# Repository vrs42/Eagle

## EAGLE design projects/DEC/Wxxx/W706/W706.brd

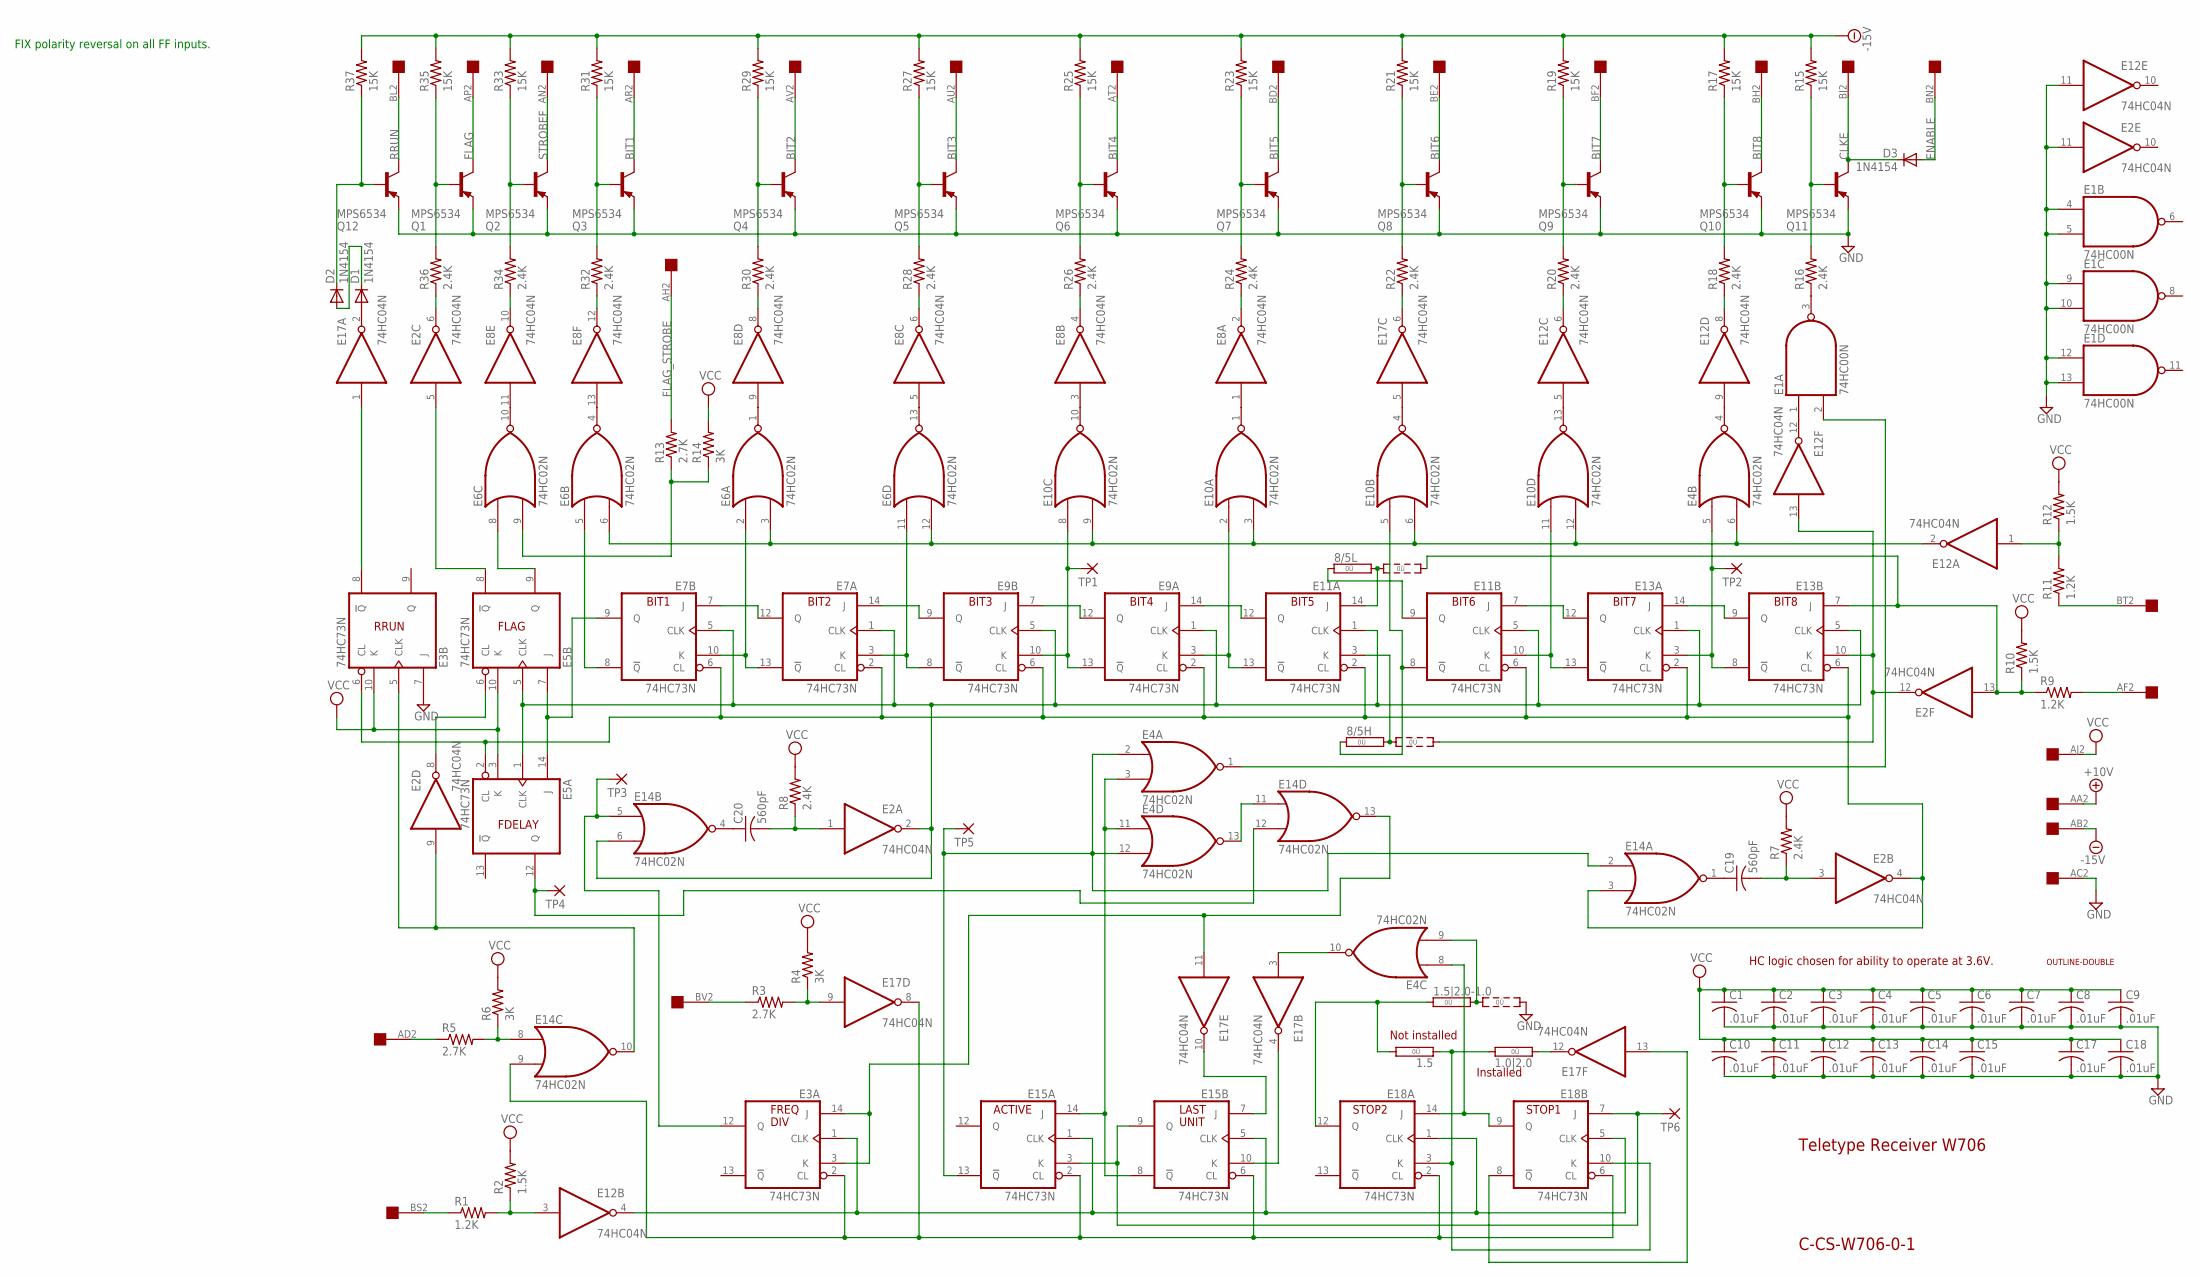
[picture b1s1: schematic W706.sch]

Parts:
1.0|2.0, 1.5: 0R; 0R/10
1.5|2.0-1.0, 8/5H, 8/5L: 0R2; 0R2/10
C1, C2, C3, C4, C5, C6, C7, C8, C9, C10, C11, C12, C13, C14, C15, C17, C18: .01uF; C050-025X075
C19, C20: 560pF; C050-025X075
D1, D2, D3: 1N4154; DO35-10
E1: 74HC00N; DIL14
E2, E8, E12, E17: 74HC04N; DIL14
E3, E5, E7, E9, E11, E13, E15, E18: 74HC73N; DIL14
E4, E6, E10, E14: 74HC02N; DIL14
Q1, Q2, Q3, Q4, Q5, Q6, Q7, Q8, Q9, Q10, Q11, Q12: MPS6534; TO39
R1, R9, R11: 1.2K; 0207/10
R2, R10, R12: 1.5K; 0207/10
R3, R5, R13: 2.7K; 0207/10
R4, R6, R14: 3K; 0207/10
R7, R8, R16, R18, R20, R22, R24, R26, R28, R30, R32, R34, R36: 2.4K; 0207/10
R15, R17, R19, R21, R23, R25, R27, R29, R31, R33, R35, R37: 15K; 0207/10
TP1, TP2, TP3, TP4, TP5, TP6: 3,17/1,3
U$1: OUTLINE-DOUBLE; DOUBLE
U$2: DOUBLE; EDGE-CON4

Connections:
+10V: U$2.AA2
-15V: R15.2, R17.2, R19.2, R21.2, R23.2, R25.2, R27.2, R29.2, R31.2, R33.2, R35.2, R37.2, U$2.AB2
BIT1: Q3.3 (C), U$2.AR2
BIT2: Q4.3 (C), U$2.AV2
BIT3: Q5.3 (C), U$2.AU2
BIT4: Q6.3 (C), U$2.AT2
BIT5: Q7.3 (C), U$2.BD2
BIT6: Q8.3 (C), U$2.BE2
BIT7: Q9.3 (C), U$2.BF2
BIT8: Q10.3 (C), U$2.BH2
CLKE: D3.C, Q11.3 (C), U$2.BJ2
ENABLE: D3.A, U$2.BN2
FLAG: Q1.3 (C), U$2.AP2
FLAG_STROBE: R13.2, U$2.AH2
GND: 1.5|2.0-1.0.3, C1.2, C2.2, C3.2, C4.2, C5.2, C6.2, C7.2, C8.2, C9.2, C10.2, C11.2, C12.2, C13.2, C14.2, C15.2, C17.2, C18.2, E1.4 (I0), E1.5 (I1), E1.7 (GND), E1.9 (I0), E1.10 (I1), E1.12 (I0), E1.13 (I1), E2.7 (GND), E2.11 (I), E3.7 (J), E3.11 (GND), E4.7 (GND), E5.11 (GND), E6.7 (GND), E7.11 (GND), E8.7 (GND), E9.11 (GND), E10.7 (GND), E11.11 (GND), E12.7 (GND), E12.11 (I), E13.11 (GND), E14.7 (GND), E15.11 (GND), E17.7 (GND), E18.11 (GND), Q1.1 (E), Q2.1 (E), Q3.1 (E), Q4.1 (E), Q5.1 (E), Q6.1 (E), Q7.1 (E), Q8.1 (E), Q9.1 (E), Q10.1 (E), Q11.1 (E), Q12.1 (E), U$2.AC2
unnamed: E6.1 (O), E8.9 (I)
unnamed: E6.4 (O), E8.13 (I)
unnamed: E6.10 (O), E8.11 (I)
unnamed: E6.13 (O), E8.5 (I)
unnamed: E8.1 (I), E10.1 (O)
unnamed: E10.4 (O), E17.5 (I)
unnamed: E10.13 (O), E12.5 (I)
unnamed: E8.3 (I), E10.10 (O)
unnamed: E4.4 (O), E12.9 (I)
unnamed: D1.A, E17.2 (O)
unnamed: D1.C, D2.A
unnamed: D2.C, Q12.2 (B), R37.1
unnamed: E1.3 (O), R16.1
unnamed: E12.8 (O), R18.1
unnamed: E12.6 (O), R20.1
unnamed: E17.6 (O), R22.1
unnamed: E8.2 (O), R24.1
unnamed: E8.4 (O), R26.1
unnamed: E8.6 (O), R28.1
unnamed: E8.8 (O), R30.1
unnamed: E8.12 (O), R32.1
unnamed: E2.6 (O), R36.1
unnamed: Q1.2 (B), R35.1, R36.2
unnamed: E8.10 (O), R34.1
unnamed: Q2.2 (B), R33.1, R34.2
unnamed: Q3.2 (B), R31.1, R32.2
unnamed: Q4.2 (B), R29.1, R30.2
unnamed: Q5.2 (B), R27.1, R28.2
unnamed: Q6.2 (B), R25.1, R26.2
unnamed: Q7.2 (B), R23.1, R24.2
unnamed: Q8.2 (B), R21.1, R22.2
unnamed: Q9.2 (B), R19.1, R20.2
unnamed: Q10.2 (B), R17.1, R18.2
unnamed: Q11.2 (B), R15.1, R16.2
unnamed: E3.8 (!Q), E17.1 (I)
unnamed: E2.5 (I), E5.8 (!Q)
unnamed: E5.9 (Q), E6.8 (I0)
unnamed: E7.7 (J), E7.12 (Q)
unnamed: E6.2 (I0), E7.10 (K), E7.13 (!Q)
unnamed: E2.2 (O), E5.1 (CLK), E5.5 (CLK), E7.1 (CLK), E7.5 (CLK), E9.1 (CLK), E9.5 (CLK), E11.1 (CLK), E11.5 (CLK), E13.1 (CLK), E13.5 (CLK), E14.6 (I1)
unnamed: E2.4 (O), E3.6 (CL), E5.2 (CL), E7.2 (CL), E7.6 (CL), E9.2 (CL), E9.6 (CL), E11.2 (CL), E11.6 (CL), E13.2 (CL), E13.6 (CL), E14.3 (I1)
unnamed: E6.11 (I0), E7.3 (K), E9.8 (!Q)
unnamed: E7.14 (J), E9.9 (Q)
unnamed: E9.10 (K), E9.13 (!Q), E10.8 (I0), TP1.1
unnamed: E9.7 (J), E9.12 (Q)
unnamed: E10.11 (I0), E11.10 (K), E13.13 (!Q)
unnamed: E11.7 (J), E13.12 (Q)
unnamed: E9.3 (K), E10.2 (I0), E11.13 (!Q)
unnamed: E9.14 (J), E11.12 (Q)
unnamed: 8/5H.1, E10.5 (I0), E11.8 (!Q)
unnamed: 8/5L.1, E11.9 (Q)
unnamed: E4.5 (I0), E13.3 (K), E13.8 (!Q), TP2.1
unnamed: E13.9 (Q), E13.14 (J)
unnamed: R1.1, U$2.BS2
unnamed: E4.6 (I1), E6.3 (I1), E6.6 (I1), E6.12 (I1), E10.3 (I1), E10.6 (I1), E10.9 (I1), E10.12 (I1), E12.2 (O)
unnamed: E6.5 (I0), E7.8 (!Q)
unnamed: E12.3 (I), R1.2, R2.1
unnamed: R11.1, U$2.BT2
unnamed: E12.1 (I), R11.2, R12.1
unnamed: E4.3 (I1), E4.11 (I0), E15.8 (!Q), E15.14 (J)
unnamed: E2.9 (I), E3.5 (CLK), E14.10 (O)
unnamed: E4.8 (I0), E18.9 (Q), E18.14 (J)
unnamed: E15.3 (K), E15.9 (Q), E18.7 (J), TP6.1
unnamed: E1.2 (I1), E4.1 (O)
unnamed: 8/5L.3, E2.13 (I), E13.7 (J), R9.1, R10.1
unnamed: 8/5H.2, E11.3 (K)
unnamed: 8/5L.2, E11.14 (J)
unnamed: E14.8 (I0), R5.2, R6.1
unnamed: R9.2, U$2.AF2
unnamed: 8/5H.3, E2.12 (O), E12.13 (I), E13.10 (K)
unnamed: E6.9 (I1), R13.1, R14.1
unnamed: R5.1, U$2.AD2
unnamed: E4.2 (I0), E4.12 (I1), E14.2 (I0), E15.13 (!Q), TP5.1
unnamed: E2.8 (O), E5.6 (CL)
unnamed: E3.1 (CLK), E12.4 (O), E15.1 (CLK), E15.5 (CLK), E18.1 (CLK), E18.5 (CLK)
unnamed: 1.5|2.0-1.0.2, E4.9 (I1)
unnamed: E17.9 (I), R3.2, R4.1
unnamed: R3.1, U$2.BV2
unnamed: E4.10 (O), E17.3 (I)
unnamed: E3.2 (CL), E14.9 (I1), E15.2 (CL), E15.6 (CL), E17.8 (O), E18.2 (CL), E18.6 (CL)
unnamed: 1.0|2.0.2, 1.5.1, E18.3 (K), E18.10 (K)
unnamed: 1.5.2, 1.5|2.0-1.0.1, E18.12 (Q)
unnamed: E15.10 (K), E17.4 (O)
unnamed: E4.13 (O), E14.11 (I0)
unnamed: C20.2, E2.1 (I), R8.1
unnamed: C19.2, E2.3 (I), R7.1
unnamed: C20.1, E14.4 (O)
unnamed: C19.1, E14.1 (O)
unnamed: 1.0|2.0.1, E17.12 (O)
unnamed: E17.13 (I), E18.8 (!Q)
unnamed: E3.12 (Q), E14.5 (I0), TP3.1
unnamed: E5.7 (J), E5.14 (J), E7.9 (Q)
unnamed: E15.7 (J), E17.10 (O)
unnamed: E5.12 (Q), E14.12 (I1), TP4.1
unnamed: E3.3 (K), E3.14 (J), E14.13 (O), E17.11 (I)
unnamed: E1.1 (I0), E12.12 (O)
RRUN: Q12.3 (C), U$2.BL2
STROBEF: Q2.3 (C), U$2.AN2
VCC: C1.1, C2.1, C3.1, C4.1, C5.1, C6.1, C7.1, C8.1, C9.1, C10.1, C11.1, C12.1, C13.1, C14.1, C15.1, C17.1, C18.1, E1.14 (VCC), E2.14 (VCC), E3.4 (VCC), E3.10 (K), E4.14 (VCC), E5.3 (K), E5.4 (VCC), E5.10 (K), E6.14 (VCC), E7.4 (VCC), E8.14 (VCC), E9.4 (VCC), E10.14 (VCC), E11.4 (VCC), E12.14 (VCC), E13.4 (VCC), E14.14 (VCC), E15.4 (VCC), E17.14 (VCC), E18.4 (VCC), R2.2, R4.2, R6.2, R7.2, R8.2, R10.2, R12.2, R14.2, U$2.AJ2

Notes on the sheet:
Teletype Receiver W706
C-CS-W706-0-1
BIT1
BIT2
BIT3
BIT4
BIT5
BIT6
BIT7
BIT8
RRUN
FLAG
FDELAY
STOP1
STOP2
LAST
UNIT
ACTIVE
FREQ
DIV
Not installed
Installed
HC logic chosen for ability to operate at 3.6V.
FIX polarity reversal on all FF inputs.

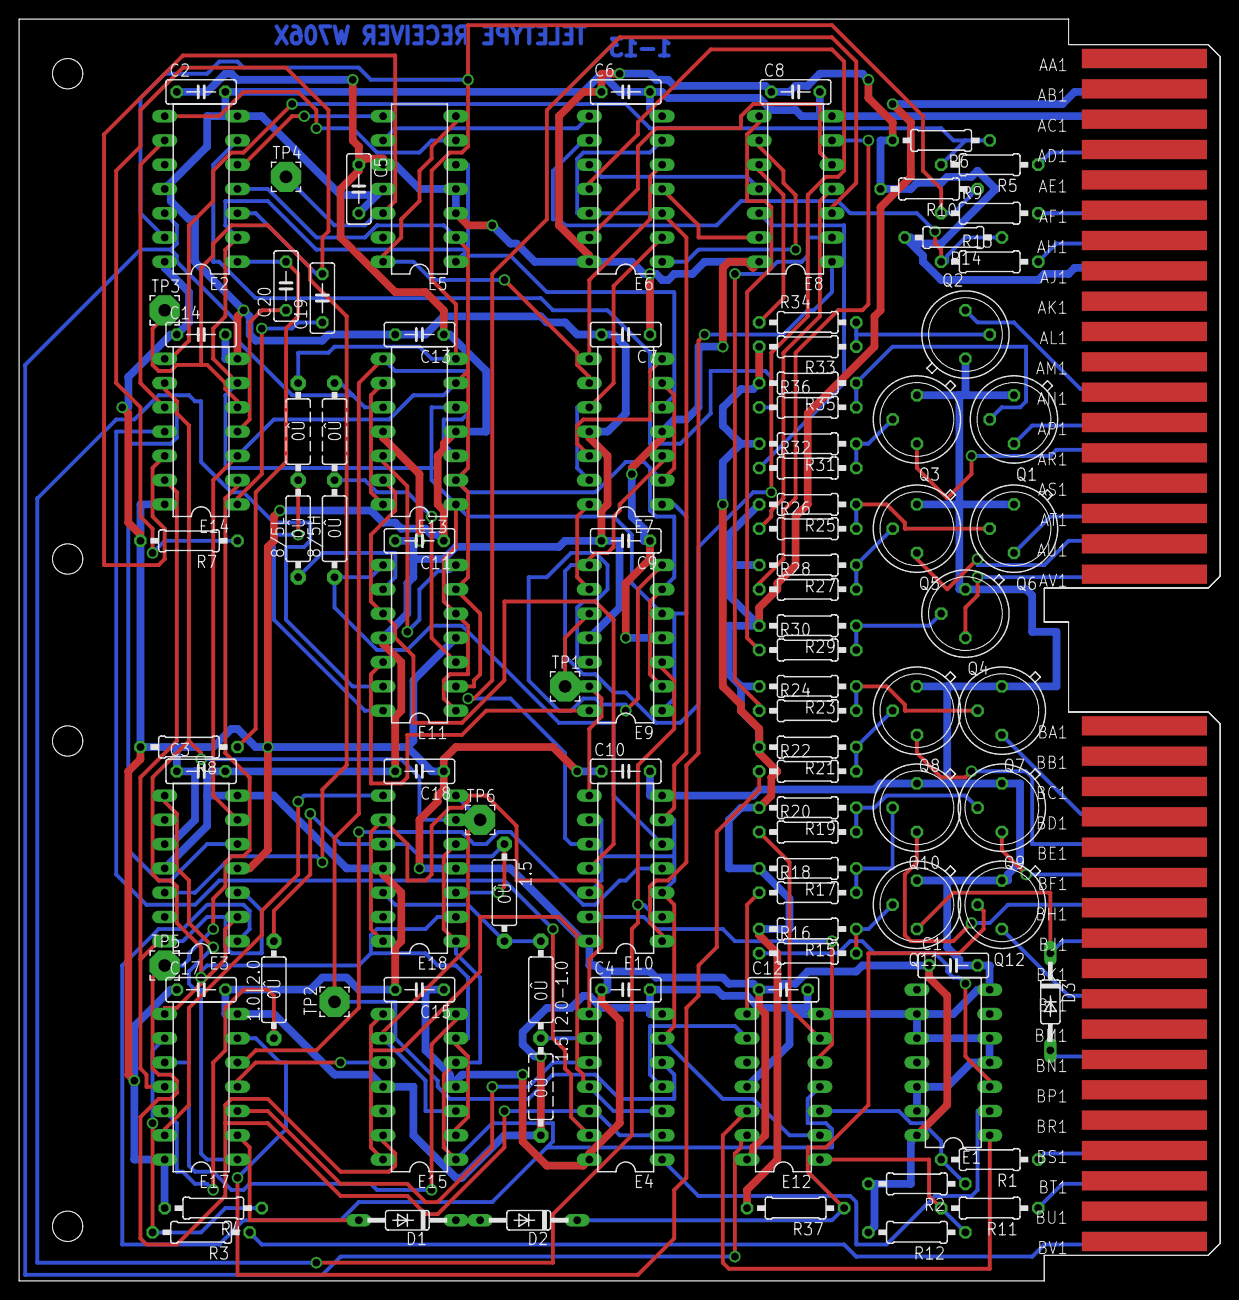
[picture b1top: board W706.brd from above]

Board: 2 copper layers, 125.7 x 132.1 mm, 101 parts (0 on the bottom side), 113 nets.

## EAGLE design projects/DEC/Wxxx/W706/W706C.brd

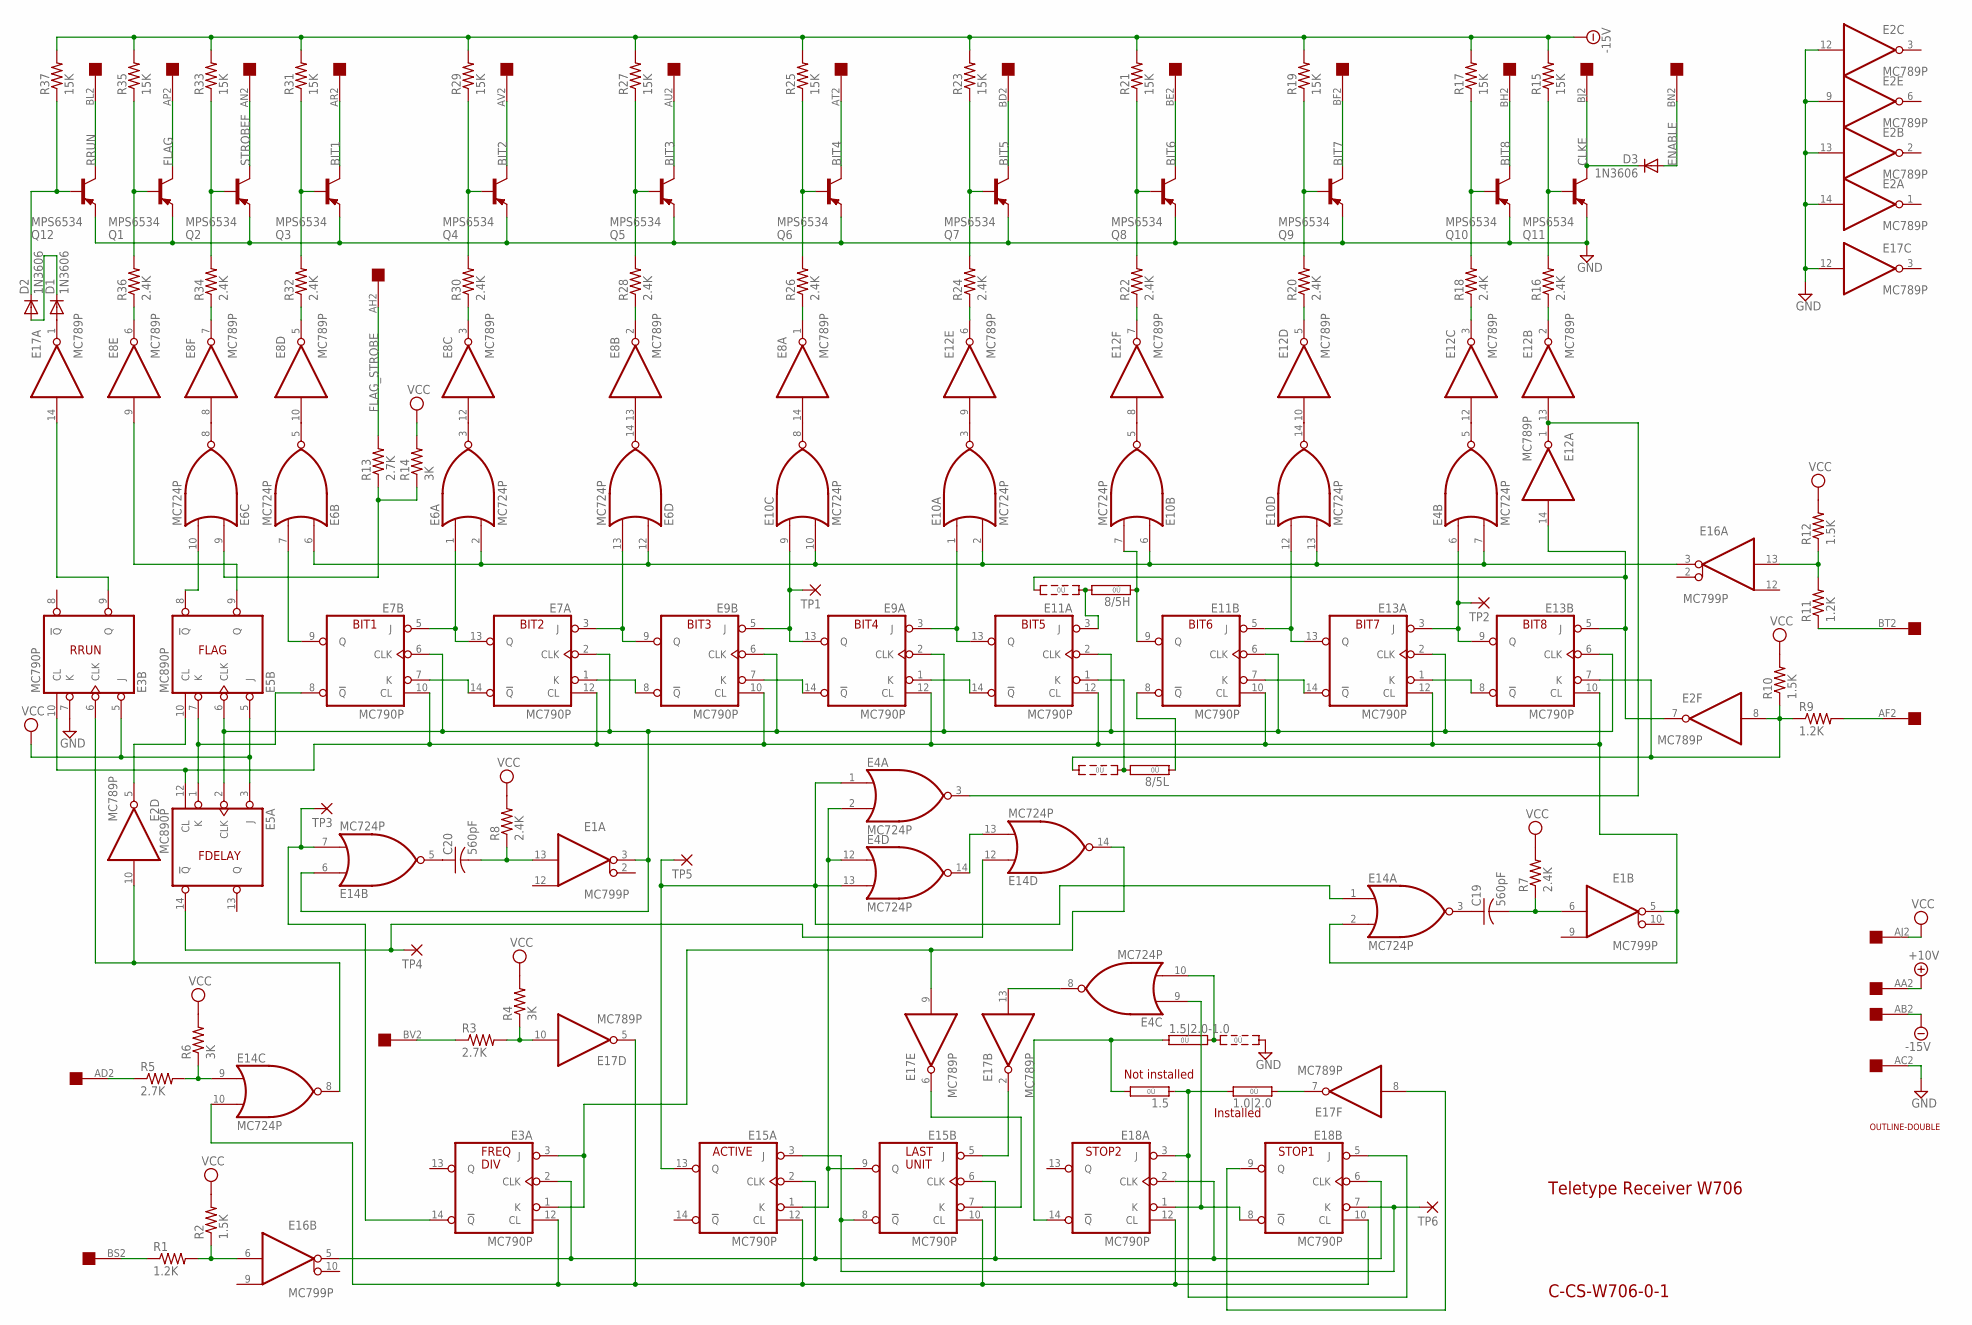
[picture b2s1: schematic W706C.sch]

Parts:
1.0|2.0, 1.5: 0R; 0R/10
1.5|2.0-1.0, 8/5H, 8/5L: 0R2; 0R2/10
C19, C20: 560pF; C050-025X075
D1, D2, D3: 1N3606; DO35-10
E1, E16: MC799P; DIL14
E2, E8, E12, E17: MC789P; DIL14
E3, E7, E9, E11, E13, E15, E18: MC790P; DIL14
E4, E6, E10, E14: MC724P; DIL14
E5: MC890P; DIL14
Q1, Q2, Q3, Q4, Q5, Q6, Q7, Q8, Q9, Q10, Q11, Q12: MPS6534; TO39
R1, R9, R11: 1.2K; 0207/10
R2, R10, R12: 1.5K; 0207/10
R3, R5, R13: 2.7K; 0207/10
R4, R6, R14: 3K; 0207/10
R7, R8, R16, R18, R20, R22, R24, R26, R28, R30, R32, R34, R36: 2.4K; 0207/10
R15, R17, R19, R21, R23, R25, R27, R29, R31, R33, R35, R37: 15K; 0207/10
TP1, TP2, TP3, TP4, TP5, TP6: 3,17/1,3
U$1: OUTLINE-DOUBLE; DOUBLE
U$2: DOUBLE; EDGE-CON4

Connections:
+10V: U$2.AA2
-15V: R15.2, R17.2, R19.2, R21.2, R23.2, R25.2, R27.2, R29.2, R31.2, R33.2, R35.2, R37.2, U$2.AB2
BIT1: Q3.3 (C), U$2.AR2
BIT2: Q4.3 (C), U$2.AV2
BIT3: Q5.3 (C), U$2.AU2
BIT4: Q6.3 (C), U$2.AT2
BIT5: Q7.3 (C), U$2.BD2
BIT6: Q8.3 (C), U$2.BE2
BIT7: Q9.3 (C), U$2.BF2
BIT8: Q10.3 (C), U$2.BH2
CLKE: D3.C, Q11.3 (C), U$2.BJ2
ENABLE: D3.A, U$2.BN2
FLAG: Q1.3 (C), U$2.AP2
FLAG_STROBE: R13.2, U$2.AH2
GND: 1.5|2.0-1.0.3, E1.4 (GND), E2.4 (GND), E2.9 (I), E2.12 (I), E2.13 (I), E2.14 (I), E3.4 (GND), E3.7 (K), E4.4 (GND), E5.4 (GND), E6.4 (GND), E7.4 (GND), E8.4 (GND), E9.4 (GND), E10.4 (GND), E11.4 (GND), E12.4 (GND), E13.4 (GND), E14.4 (GND), E15.4 (GND), E16.4 (GND), E17.4 (GND), E17.12 (I), E18.4 (GND), Q1.1 (E), Q2.1 (E), Q3.1 (E), Q4.1 (E), Q5.1 (E), Q6.1 (E), Q7.1 (E), Q8.1 (E), Q9.1 (E), Q10.1 (E), Q11.1 (E), Q12.1 (E), U$2.AC2
unnamed: E6.3 (O), E8.12 (I)
unnamed: E6.5 (O), E8.10 (I)
unnamed: E6.8 (O), E8.8 (I)
unnamed: E6.14 (O), E8.13 (I)
unnamed: E10.3 (O), E12.9 (I)
unnamed: E10.5 (O), E12.8 (I)
unnamed: E10.14 (O), E12.10 (I)
unnamed: E8.14 (I), E10.8 (O)
unnamed: E4.5 (O), E12.12 (I)
unnamed: D1.A, E17.1 (O)
unnamed: D1.C, D2.A
unnamed: D2.C, Q12.2 (B), R37.1
unnamed: E12.2 (O), R16.1
unnamed: E12.3 (O), R18.1
unnamed: E12.5 (O), R20.1
unnamed: E12.7 (O), R22.1
unnamed: E12.6 (O), R24.1
unnamed: E8.1 (O), R26.1
unnamed: E8.2 (O), R28.1
unnamed: E8.3 (O), R30.1
unnamed: E8.5 (O), R32.1
unnamed: E8.6 (O), R36.1
unnamed: Q1.2 (B), R35.1, R36.2
unnamed: E8.7 (O), R34.1
unnamed: Q2.2 (B), R33.1, R34.2
unnamed: Q3.2 (B), R31.1, R32.2
unnamed: Q4.2 (B), R29.1, R30.2
unnamed: Q5.2 (B), R27.1, R28.2
unnamed: Q6.2 (B), R25.1, R26.2
unnamed: Q7.2 (B), R23.1, R24.2
unnamed: Q8.2 (B), R21.1, R22.2
unnamed: Q9.2 (B), R19.1, R20.2
unnamed: Q10.2 (B), R17.1, R18.2
unnamed: Q11.2 (B), R15.1, R16.2
unnamed: E3.9 (Q), E17.14 (I)
unnamed: E5.9 (Q), E8.9 (I)
unnamed: E5.8 (!Q), E6.10 (I1)
unnamed: E7.7 (K), E7.14 (!Q)
unnamed: E6.1 (I0), E7.5 (J), E7.13 (Q)
unnamed: E1.3 (O), E5.2 (CLK), E5.6 (CLK), E7.2 (CLK), E7.6 (CLK), E9.2 (CLK), E9.6 (CLK), E11.2 (CLK), E11.6 (CLK), E13.2 (CLK), E13.6 (CLK), E14.6 (I0)
unnamed: E1.5 (O), E3.10 (CL), E5.12 (CL), E7.10 (CL), E7.12 (CL), E9.10 (CL), E9.12 (CL), E11.10 (CL), E11.12 (CL), E13.10 (CL), E13.12 (CL), E14.2 (I1)
unnamed: E6.13 (I1), E7.3 (J), E9.9 (Q)
unnamed: E7.1 (K), E9.8 (!Q)
unnamed: E9.5 (J), E9.13 (Q), E10.9 (I0), TP1.1
unnamed: E9.7 (K), E9.14 (!Q)
unnamed: E10.12 (I0), E11.5 (J), E13.13 (Q)
unnamed: E11.7 (K), E13.14 (!Q)
unnamed: E9.3 (J), E10.1 (I0), E11.13 (Q)
unnamed: E9.1 (K), E11.14 (!Q)
unnamed: 8/5H.1, E10.7 (I1), E11.9 (Q)
unnamed: 8/5L.1, E11.8 (!Q)
unnamed: E4.6 (I0), E13.3 (J), E13.9 (Q), TP2.1
unnamed: E13.1 (K), E13.8 (!Q)
unnamed: R1.1, U$2.BS2
unnamed: E4.7 (I1), E6.2 (I1), E6.6 (I0), E6.12 (I0), E10.2 (I1), E10.6 (I0), E10.10 (I1), E10.13 (I1), E16.3 (O)
unnamed: E6.7 (I1), E7.9 (Q)
unnamed: E16.6 (I), R1.2, R2.1
unnamed: R11.1, U$2.BT2
unnamed: E16.13 (I), R11.2, R12.1
unnamed: E4.2 (I1), E4.12 (I0), E15.1 (K), E15.9 (Q)
unnamed: E2.10 (I), E3.6 (CLK), E14.8 (O)
unnamed: E4.9 (I0), E18.1 (K), E18.8 (!Q)
unnamed: E15.3 (J), E15.8 (!Q), E18.7 (K), TP6.1
unnamed: E4.3 (O), E12.1 (O), E12.13 (I)
unnamed: 8/5L.3, E2.8 (I), E13.7 (K), R9.1, R10.1
unnamed: 8/5H.2, E11.3 (J)
unnamed: 8/5L.2, E11.1 (K)
unnamed: E14.9 (I0), R5.2, R6.1
unnamed: R9.2, U$2.AF2
unnamed: 8/5H.3, E2.7 (O), E12.14 (I), E13.5 (J)
unnamed: E6.9 (I0), R13.1, R14.1
unnamed: R5.1, U$2.AD2
unnamed: E4.1 (I0), E4.13 (I1), E14.1 (I0), E15.13 (Q), TP5.1
unnamed: E2.5 (O), E5.10 (CL)
unnamed: E3.2 (CLK), E15.2 (CLK), E15.6 (CLK), E16.5 (O), E18.2 (CLK), E18.6 (CLK)
unnamed: 1.5|2.0-1.0.2, E4.10 (I1)
unnamed: E17.10 (I), R3.2, R4.1
unnamed: R3.1, U$2.BV2
unnamed: E4.8 (O), E17.13 (I)
unnamed: E3.12 (CL), E14.10 (I1), E15.10 (CL), E15.12 (CL), E17.5 (O), E18.10 (CL), E18.12 (CL)
unnamed: 1.0|2.0.2, 1.5.1, E18.3 (J), E18.5 (J)
unnamed: 1.5.2, 1.5|2.0-1.0.1, E18.14 (!Q)
unnamed: E15.5 (J), E17.2 (O)
unnamed: E4.14 (O), E14.13 (I1)
unnamed: C20.2, E1.13 (I), R8.1
unnamed: C19.2, E1.6 (I), R7.1
unnamed: C20.1, E14.5 (O)
unnamed: C19.1, E14.3 (O)
unnamed: 1.0|2.0.1, E17.7 (O)
unnamed: E17.8 (I), E18.9 (Q)
unnamed: E3.14 (!Q), E14.7 (I1), TP3.1
unnamed: E5.1 (K), E5.7 (K), E7.8 (!Q)
unnamed: E15.7 (K), E17.6 (O)
unnamed: E5.14 (!Q), E14.12 (I0), TP4.1
unnamed: E3.1 (K), E3.3 (J), E14.14 (O), E17.9 (I)
RRUN: Q12.3 (C), U$2.BL2
STROBEF: Q2.3 (C), U$2.AN2
VCC: E1.11 (VCC), E2.11 (VCC), E3.5 (J), E3.11 (VCC), E4.11 (VCC), E5.3 (J), E5.5 (J), E5.11 (VCC), E6.11 (VCC), E7.11 (VCC), E8.11 (VCC), E9.11 (VCC), E10.11 (VCC), E11.11 (VCC), E12.11 (VCC), E13.11 (VCC), E14.11 (VCC), E15.11 (VCC), E16.11 (VCC), E17.11 (VCC), E18.11 (VCC), R2.2, R4.2, R6.2, R7.2, R8.2, R10.2, R12.2, R14.2, U$2.AJ2

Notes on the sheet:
Teletype Receiver W706
C-CS-W706-0-1
BIT1
BIT2
BIT3
BIT4
BIT5
BIT6
BIT7
BIT8
RRUN
FLAG
FDELAY
STOP1
STOP2
LAST
UNIT
ACTIVE
FREQ
DIV
Not installed
Installed

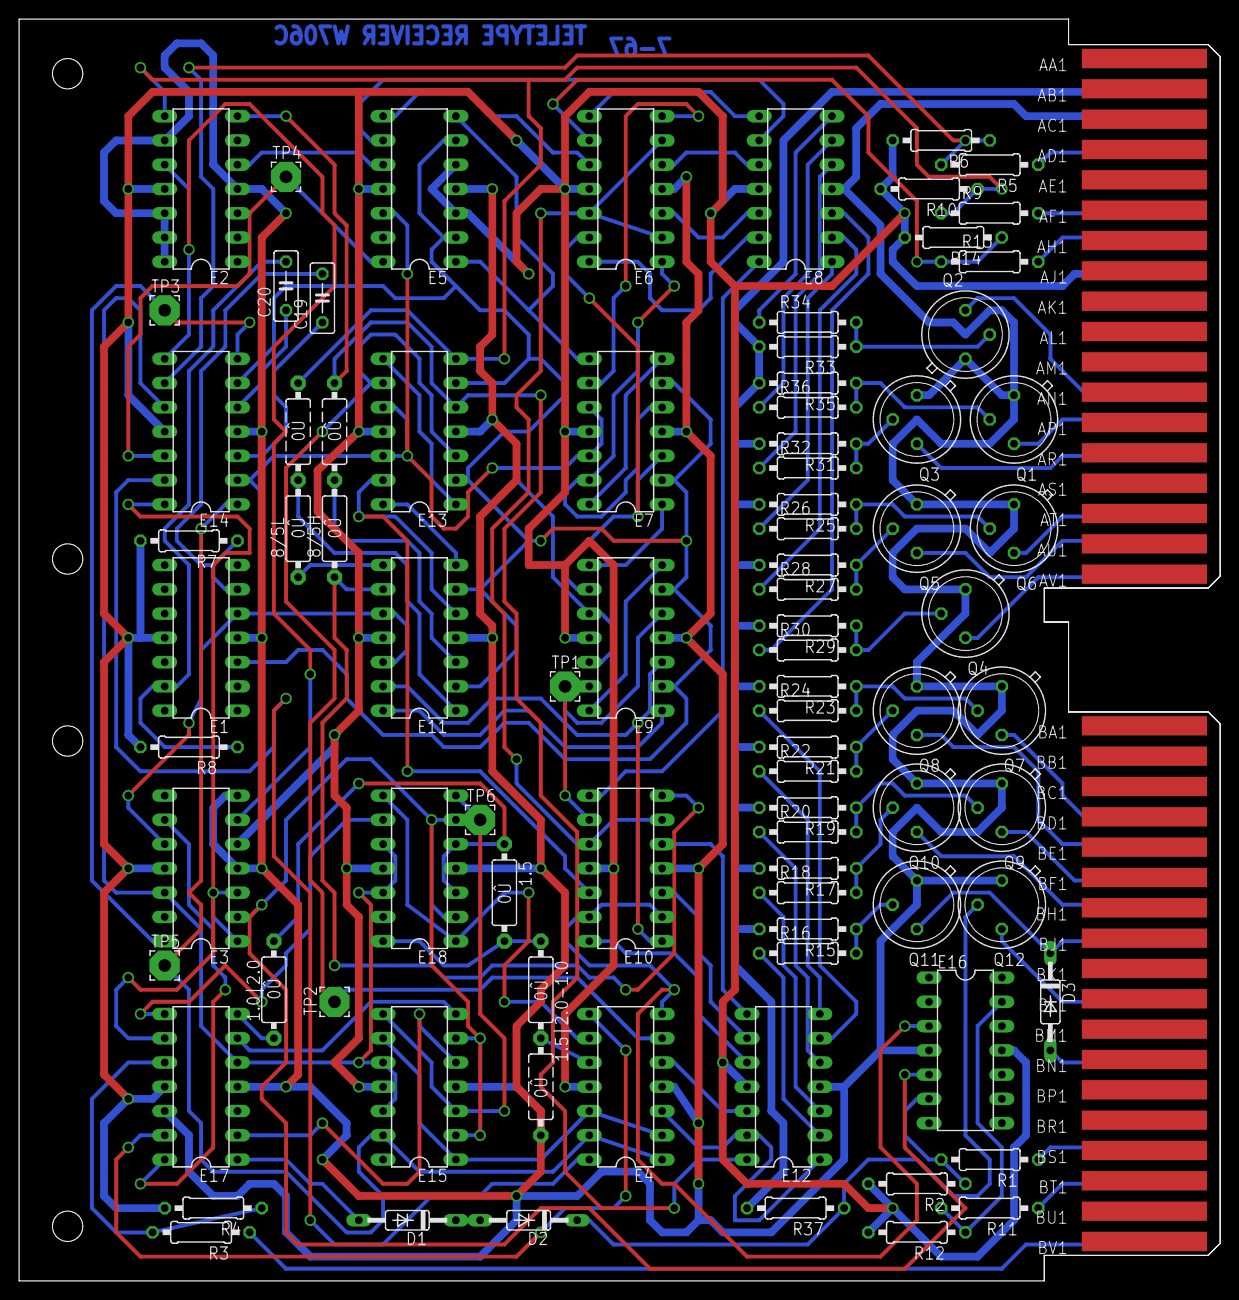
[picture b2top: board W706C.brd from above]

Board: 2 copper layers, 125.7 x 132.1 mm, 85 parts (0 on the bottom side), 112 nets.

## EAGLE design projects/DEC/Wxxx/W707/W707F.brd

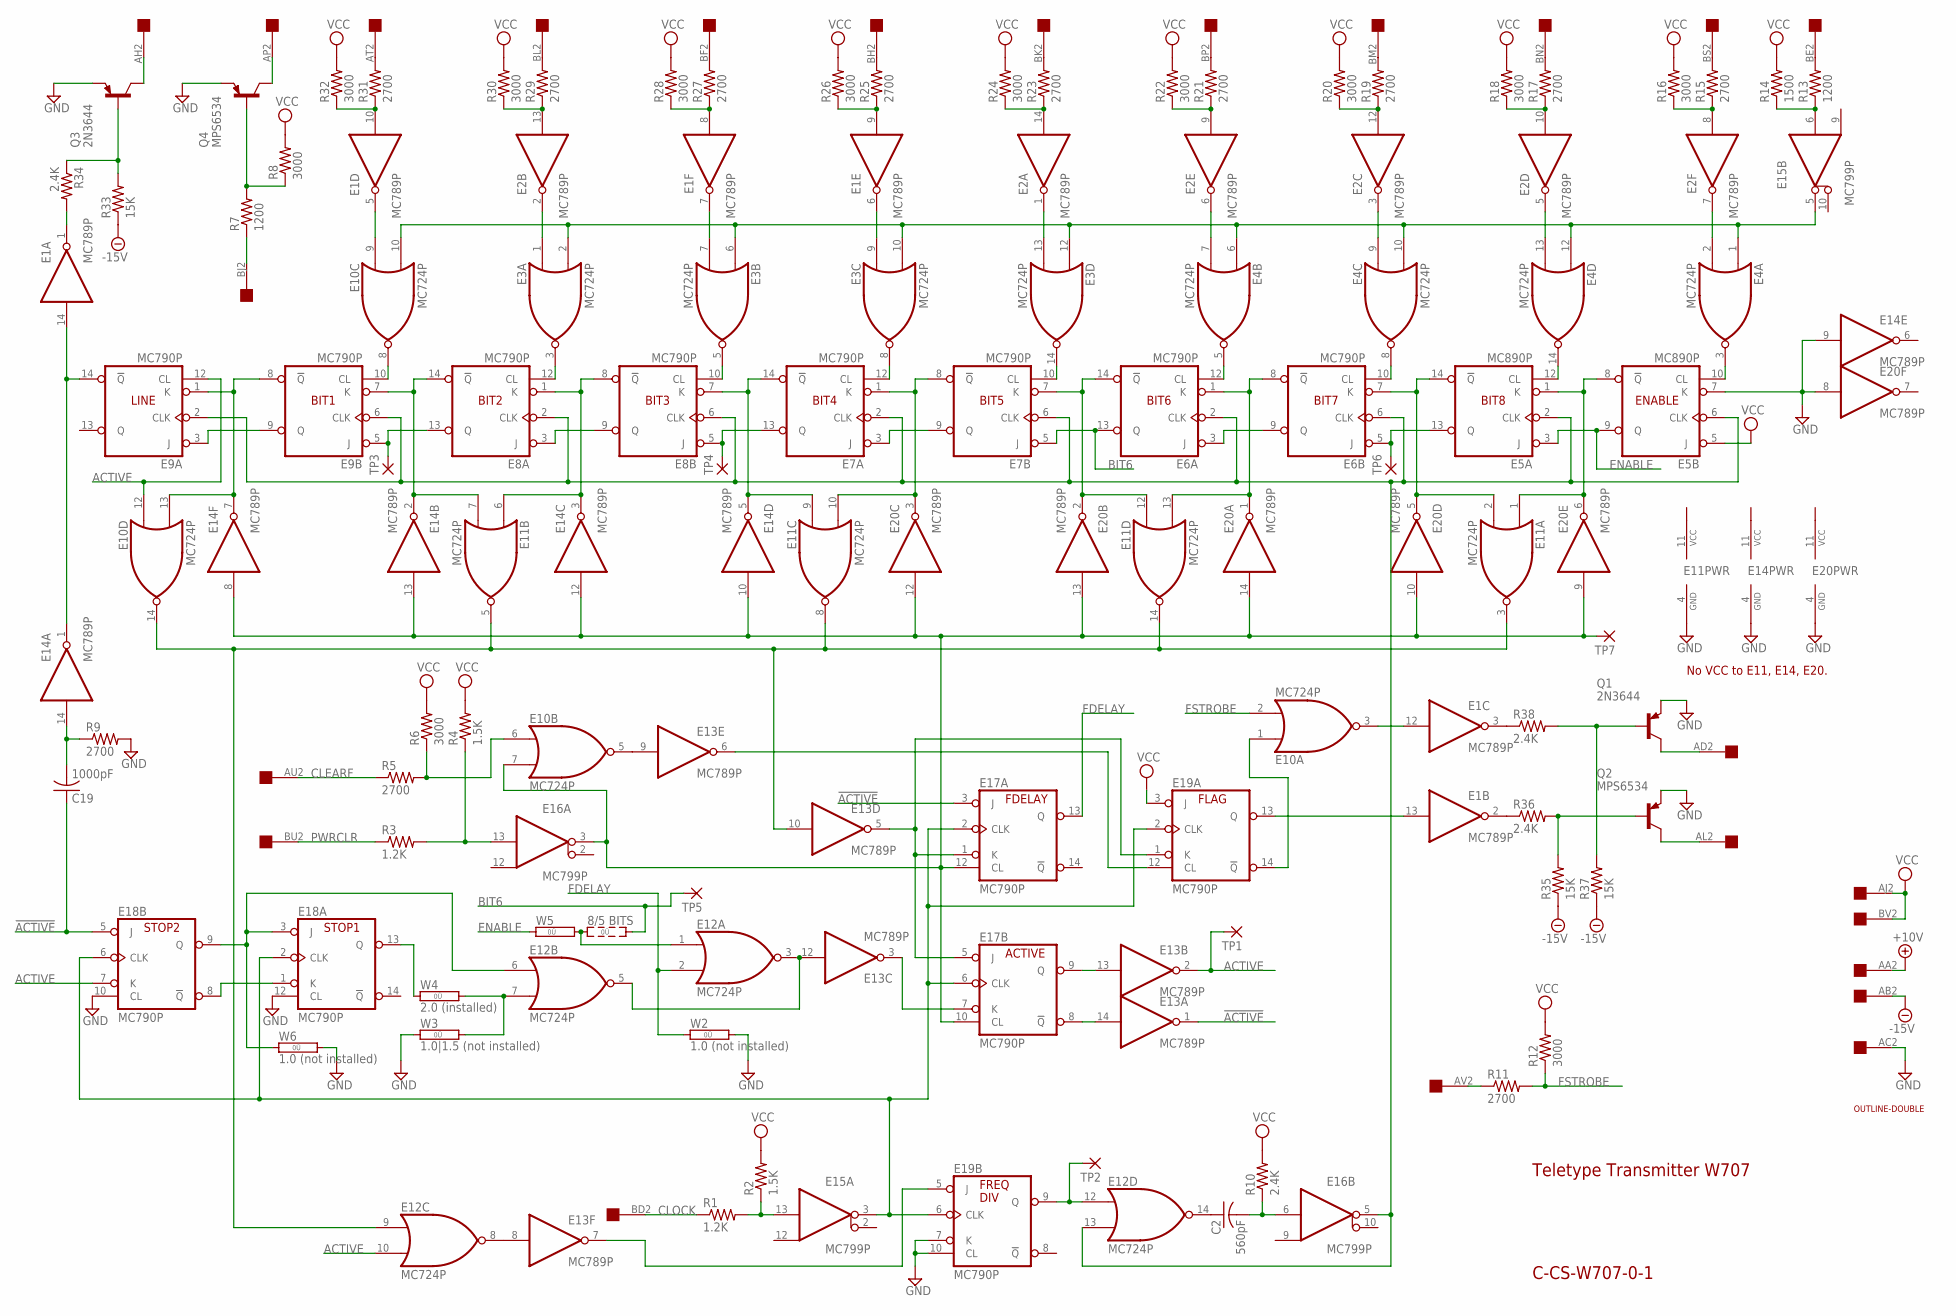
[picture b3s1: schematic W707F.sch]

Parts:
C2: 560pF; C050-025X075
C19: 1000pF; C050-025X075
E1, E2, E13, E14, E20: MC789P; DIL14
E3, E4, E10, E11, E12: MC724P; DIL14
E5: MC890P; DIL14
E6, E7, E8, E9, E17, E18, E19: MC790P; DIL14
E15, E16: MC799P; DIL14
Q1, Q3: 2N3644; TO39
Q2, Q4: MPS6534; TO39
R1, R3: 1.2K; 0207/10
R2, R4: 1.5K; 0207/10
R5, R9, R11, R15, R17, R19, R21, R23, R25, R27, R29, R31: 2700; 0207/10
R6, R8, R12, R16, R18, R20, R22, R24, R26, R28, R30, R32: 3000; 0207/10
R7, R13: 1200; 0207/10
R10, R34, R36, R38: 2.4K; 0207/10
R14: 1500; 0207/10
R33, R35, R37: 15K; 0207/10
TP1, TP2, TP3, TP4, TP5, TP6, TP7: 3,17/1,3
U$1: OUTLINE-DOUBLE; DOUBLE
U$2: DOUBLE; EDGE-CON4
W2, W6: 1.0 (not installed); 0R/10
W3: 1.0|1.5 (not installed); 0R/10
W4: 2.0 (installed); 0R/10
W5: 8/5 BITS; 0R2/10

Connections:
!ACTIVE: C19.1, E13.1 (O), E17.3 (J), E18.5 (J)
+10V: U$2.AA2
-15V: R33.1, R35.1, R37.1, U$2.AB2
ACTIVE: E9.12 (CL), E10.12 (I0), E12.10 (I1), E13.2 (O), E18.7 (K), TP1.1
BIT6: E6.13 (Q), E7.5 (J), TP5.1, W5.3
CLEARF: R5.1, U$2.AU2
CLOCK: R1.1, U$2.BD2
ENABLE: E5.3 (J), E5.9 (Q), W5.1
FDELAY: E12.2 (I1), E17.13 (Q), W2.1
FSTROBE: E10.2 (I1), R11.2, R12.1
GND: E1.4 (GND), E2.4 (GND), E3.4 (GND), E4.4 (GND), E5.4 (GND), E5.7 (K), E6.4 (GND), E7.4 (GND), E8.4 (GND), E9.4 (GND), E10.4 (GND), E11.4 (GND), E12.4 (GND), E13.4 (GND), E14.4 (GND), E14.9 (I), E15.4 (GND), E16.4 (GND), E17.4 (GND), E18.4 (GND), E18.10 (CL), E18.12 (CL), E19.4 (GND), E19.7 (K), E19.10 (CL), E20.4 (GND), E20.8 (I), Q1.1 (E), Q2.1 (E), Q3.1 (E), Q4.1 (E), R9.2, U$2.AC2, W2.2, W3.1, W6.2
unnamed: E1.5 (O), E10.9 (I0)
unnamed: E2.2 (O), E3.1 (I0)
unnamed: E1.7 (O), E3.7 (I1)
unnamed: E1.6 (O), E3.9 (I0)
unnamed: E2.1 (O), E3.13 (I1)
unnamed: E2.6 (O), E4.7 (I1)
unnamed: E2.3 (O), E4.9 (I0)
unnamed: E2.5 (O), E4.13 (I1)
unnamed: E2.7 (O), E4.2 (I1)
unnamed: R31.2, U$2.AT2
unnamed: R29.2, U$2.BL2
unnamed: R27.2, U$2.BF2
unnamed: E1.10 (I), R31.1, R32.1
unnamed: E1.8 (I), R27.1, R28.1
unnamed: R25.2, U$2.BH2
unnamed: E1.9 (I), R25.1, R26.1
unnamed: R23.2, U$2.BK2
unnamed: E2.14 (I), R23.1, R24.1
unnamed: E2.9 (I), R21.1, R22.1
unnamed: R21.2, U$2.BP2
unnamed: R19.2, U$2.BM2
unnamed: R17.2, U$2.BN2
unnamed: R15.2, U$2.BS2
unnamed: E2.13 (I), R29.1, R30.1
unnamed: E15.3 (O), E17.2 (CLK), E17.6 (CLK), E18.2 (CLK), E18.6 (CLK), E19.2 (CLK), E19.6 (CLK)
unnamed: E2.12 (I), R19.1, R20.1
unnamed: E2.10 (I), R17.1, R18.1
unnamed: E2.8 (I), R15.1, R16.1
unnamed: R13.2, U$2.BE2
unnamed: E15.6 (I), R13.1, R14.1
unnamed: E3.2 (I1), E3.6 (I0), E3.10 (I1), E3.12 (I0), E4.1 (I0), E4.6 (I0), E4.10 (I1), E4.12 (I0), E10.10 (I1), E15.5 (O)
unnamed: E5.2 (CLK), E5.6 (CLK), E6.2 (CLK), E6.6 (CLK), E7.2 (CLK), E7.6 (CLK), E8.2 (CLK), E8.6 (CLK), E9.2 (CLK), E9.6 (CLK), E12.13 (I1), E16.5 (O)
unnamed: E8.1 (K), E8.8 (!Q), E11.6 (I0), E14.3 (O)
unnamed: E8.3 (J), E8.9 (Q)
unnamed: E7.14 (!Q), E8.7 (K), E11.9 (I0), E14.5 (O)
unnamed: E7.13 (Q), E8.5 (J), TP4.1
unnamed: E7.3 (J), E7.9 (Q)
unnamed: E7.1 (K), E7.8 (!Q), E11.10 (I1), E20.3 (O)
unnamed: E6.14 (!Q), E7.7 (K), E11.12 (I0), E20.2 (O)
unnamed: E12.1 (I0), W5.2
unnamed: E6.1 (K), E6.8 (!Q), E11.13 (I1), E20.1 (O)
unnamed: E6.3 (J), E6.9 (Q)
unnamed: E5.14 (!Q), E6.7 (K), E11.2 (I1), E20.5 (O)
unnamed: E5.13 (Q), E6.5 (J), TP6.1
unnamed: E5.1 (K), E5.8 (!Q), E11.1 (I0), E20.6 (O)
unnamed: Q4.3 (C), U$2.AP2
unnamed: E4.3 (O), E5.10 (CL)
unnamed: E3.14 (O), E7.10 (CL)
unnamed: E4.5 (O), E6.12 (CL)
unnamed: E4.8 (O), E6.10 (CL)
unnamed: E4.14 (O), E5.12 (CL)
unnamed: E3.8 (O), E7.12 (CL)
unnamed: E13.7 (O), E19.5 (J)
unnamed: E8.14 (!Q), E9.7 (K), E11.7 (I1), E14.2 (O)
unnamed: E8.13 (Q), E9.5 (J), TP3.1
unnamed: E9.10 (CL), E10.8 (O)
unnamed: E3.5 (O), E8.10 (CL)
unnamed: E15.13 (I), R1.2, R2.1
unnamed: E16.13 (I), R3.2, R4.1
unnamed: E3.3 (O), E8.12 (CL)
unnamed: E9.1 (K), E9.8 (!Q), E10.13 (I1), E14.7 (O)
unnamed: E9.3 (J), E9.9 (Q)
unnamed: E1.14 (I), E9.14 (!Q), E14.1 (O)
unnamed: E1.1 (O), R34.2
unnamed: Q3.2 (B), R33.2, R34.1
unnamed: E10.7 (I1), E14.8 (I), E14.10 (I), E14.12 (I), E14.13 (I), E16.3 (O), E17.10 (CL), E17.12 (CL), E20.9 (I), E20.10 (I), E20.12 (I), E20.13 (I), E20.14 (I), TP7.1
unnamed: Q3.3 (C), U$2.AH2
unnamed: E10.14 (O), E11.3 (O), E11.5 (O), E11.8 (O), E11.14 (O), E12.9 (I0), E13.10 (I)
unnamed: E12.12 (I0), E19.9 (Q), TP2.1
unnamed: C2.1, E12.14 (O)
unnamed: C2.2, E16.6 (I), R10.1
unnamed: E12.8 (O), E13.8 (I)
unnamed: E13.14 (I), E17.8 (!Q)
unnamed: E13.13 (I), E17.9 (Q)
unnamed: E18.13 (Q), W4.1
unnamed: E13.3 (O), E17.7 (K)
unnamed: E12.3 (O), E12.5 (O), E13.12 (I)
unnamed: Q4.2 (B), R7.2, R8.1
unnamed: E12.6 (I0), E18.3 (J), E18.9 (Q), W6.1
unnamed: E10.1 (I0), E19.14 (!Q)
unnamed: E12.7 (I1), W3.2, W4.2
unnamed: R7.1, U$2.BJ2
unnamed: R11.1, U$2.AV2
unnamed: E10.5 (O), E13.9 (I)
unnamed: Q2.2 (B), R35.2, R36.2
unnamed: Q2.3 (C), U$2.AL2
unnamed: Q1.3 (C), U$2.AD2
unnamed: Q1.2 (B), R37.2, R38.2
unnamed: E1.3 (O), R38.1
unnamed: E1.2 (O), R36.1
unnamed: E1.12 (I), E10.3 (O)
unnamed: C19.2, E14.14 (I), R9.1
unnamed: E13.5 (O), E17.1 (K), E17.5 (J), E19.1 (K)
unnamed: E13.6 (O), E19.12 (CL)
unnamed: E1.13 (I), E19.13 (Q)
unnamed: E18.1 (K), E18.8 (!Q)
unnamed: E10.6 (I0), R5.2, R6.1
NC: E11.11 (VCC), E14.11 (VCC), E20.11 (VCC)
PWRCLR: R3.1, U$2.BU2
VCC: E1.11 (VCC), E2.11 (VCC), E3.11 (VCC), E4.11 (VCC), E5.5 (J), E5.11 (VCC), E6.11 (VCC), E7.11 (VCC), E8.11 (VCC), E9.11 (VCC), E10.11 (VCC), E12.11 (VCC), E13.11 (VCC), E15.11 (VCC), E16.11 (VCC), E17.11 (VCC), E18.11 (VCC), E19.3 (J), E19.11 (VCC), R2.2, R4.2, R6.2, R8.2, R10.2, R12.2, R14.2, R16.2, R18.2, R20.2, R22.2, R24.2, R26.2, R28.2, R30.2, R32.2, U$2.AJ2, U$2.BV2

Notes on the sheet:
Teletype Transmitter W707
C-CS-W707-0-1
BIT1
BIT2
BIT3
BIT4
BIT5
BIT6
BIT7
BIT8
FLAG
FDELAY
STOP1
STOP2
ACTIVE
FREQ
DIV
ENABLE
LINE
No VCC to E11, E14, E20.
